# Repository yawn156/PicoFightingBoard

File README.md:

# Pico Fighting Board

Small fork of the OG Pico Fighting Board.

The idea behind this fork is for use with the [Open Stick](https://github.com/OpenStickCommunity/Hardware/tree/main/Fightstick%20Case) case, packing together less features than you would get from more advanced boards but also just enough to build a fightstick (with PS4/5 support with the new Passthrough addon).

Another important aspect about this fork is the focus on manual assembly to reduce costs and wait time for the big demand in common used parts from JLCPCB's assembly.

## List of Materials
- Raspberry pi Pico x1 
- JST PH 4Pin Male Terminal x3
- Screw Terminal 5Pin x4
- Male Pin header 10Pin x2
- Male pin header 2Pin x4

For wiring you'll either use the brook 20 pin connector or have a crimping tool with a bunch of 2.8mm female spade connectors.

## Firmware 
You'll want to use the PicoFightingBoard firmware from the [GP2040-CE](https://gp2040-ce.info/#/download) project.

The pins used for the connectors on the board are:
- USB Passthrough D+ = 21
- USB Passthrough D- = 22 (automatically set from the addon)
- Extra Button = 24
- Reverse button = 25
- TP = 26 *
- LS = 27 *
- RS = 29 *
- SDA = 31 *
- SCL = 32 *

(Pins marked with * may be already set in the webconfigurator.)

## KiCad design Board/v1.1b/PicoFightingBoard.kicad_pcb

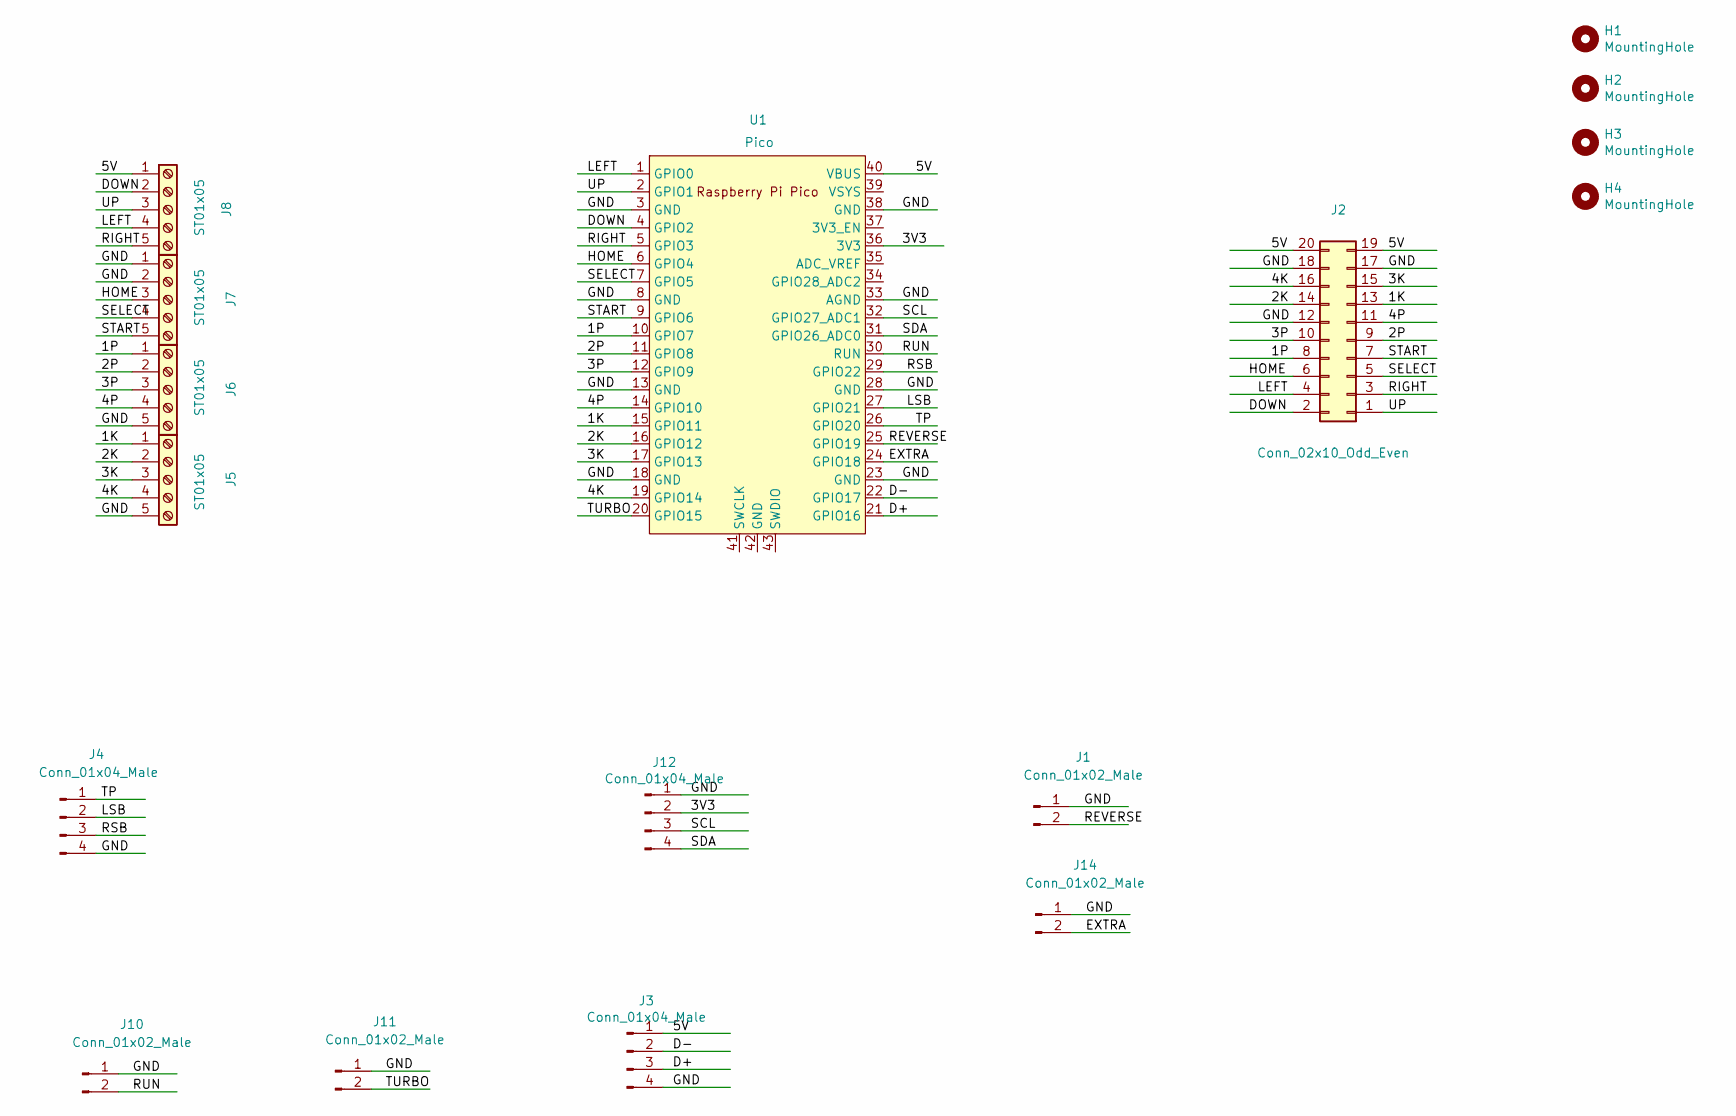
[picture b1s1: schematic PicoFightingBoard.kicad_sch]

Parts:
H1, H2, H3, H4: MountingHole; MountingHole_2.7mm_M2.5
J1, J10, J11, J14: Conn_01x02_Male; PinHeader_1x02_P2.54mm_Vertical
J2: Conn_02x10_Odd_Even; PinHeader_2x10_P2.54mm_Vertical
J3, J4, J12: Conn_01x04_Male; JST_PH_B4B-PH-K_1x04_P2.00mm_Vertical
J5, J6, J7, J8: ST01x05; TerminalBlock_MetzConnect_Type059_RT06305HBWC_1x05_P3.50mm_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
U1: Pico; RPi_Pico_SMD_TH_Clean

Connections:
/1K: J2.13, J5.1, U1.15 (GPIO11)
/1P: J2.8, J6.1, U1.10 (GPIO7)
/2K: J2.14, J5.2, U1.16 (GPIO12)
/2P: J2.9, J6.2, U1.11 (GPIO8)
/3K: J2.15, J5.3, U1.17 (GPIO13)
/3P: J2.10, J6.3, U1.12 (GPIO9)
/3V3: J12.2, U1.36 (3V3)
/4K: J2.16, J5.4, U1.19 (GPIO14)
/4P: J2.11, J6.4, U1.14 (GPIO10)
/5V: J2.19, J2.20, J3.1, J8.1, U1.40 (VBUS)
/D+: J3.3, U1.21 (GPIO16)
/D-: J3.2, U1.22 (GPIO17)
/DOWN: J2.2, J8.2, U1.4 (GPIO2)
/EXTRA: J14.2, U1.24 (GPIO18)
/GND: J1.1, J2.12, J2.17, J2.18, J3.4, J4.4, J5.5, J6.5, J7.1, J7.2, J10.1, J11.1, J12.1, J14.1, U1.3 (GND), U1.8 (GND), U1.13 (GND), U1.18 (GND), U1.23 (GND), U1.28 (GND), U1.33 (AGND), U1.38 (GND)
/HOME: J2.6, J7.3, U1.6 (GPIO4)
/LEFT: J2.4, J8.4, U1.1 (GPIO0)
/LSB: J4.2, U1.27 (GPIO21)
/REVERSE: J1.2, U1.25 (GPIO19)
/RIGHT: J2.3, J8.5, U1.5 (GPIO3)
/RSB: J4.3, U1.29 (GPIO22)
/RUN: J10.2, U1.30 (RUN)
/SCL: J12.3, U1.32 (GPIO27_ADC1)
/SDA: J12.4, U1.31 (GPIO26_ADC0)
/SELECT: J2.5, J7.4, U1.7 (GPIO5)
/START: J2.7, J7.5, U1.9 (GPIO6)
/TP: J4.1, U1.26 (GPIO20)
/TURBO: J11.2, U1.20 (GPIO15)
/UP: J2.1, J8.3, U1.2 (GPIO1)

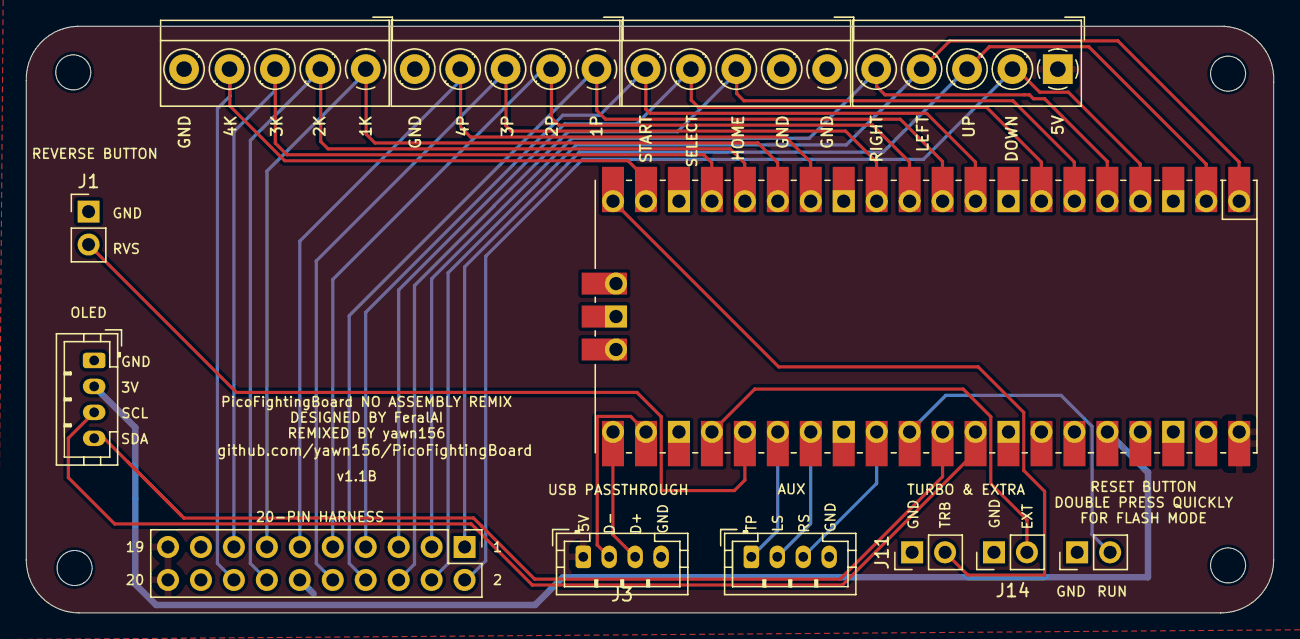
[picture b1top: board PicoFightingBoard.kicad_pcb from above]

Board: 2 copper layers, 96.1 x 45.2 mm, 17 parts (0 on the bottom side), 29 nets.
